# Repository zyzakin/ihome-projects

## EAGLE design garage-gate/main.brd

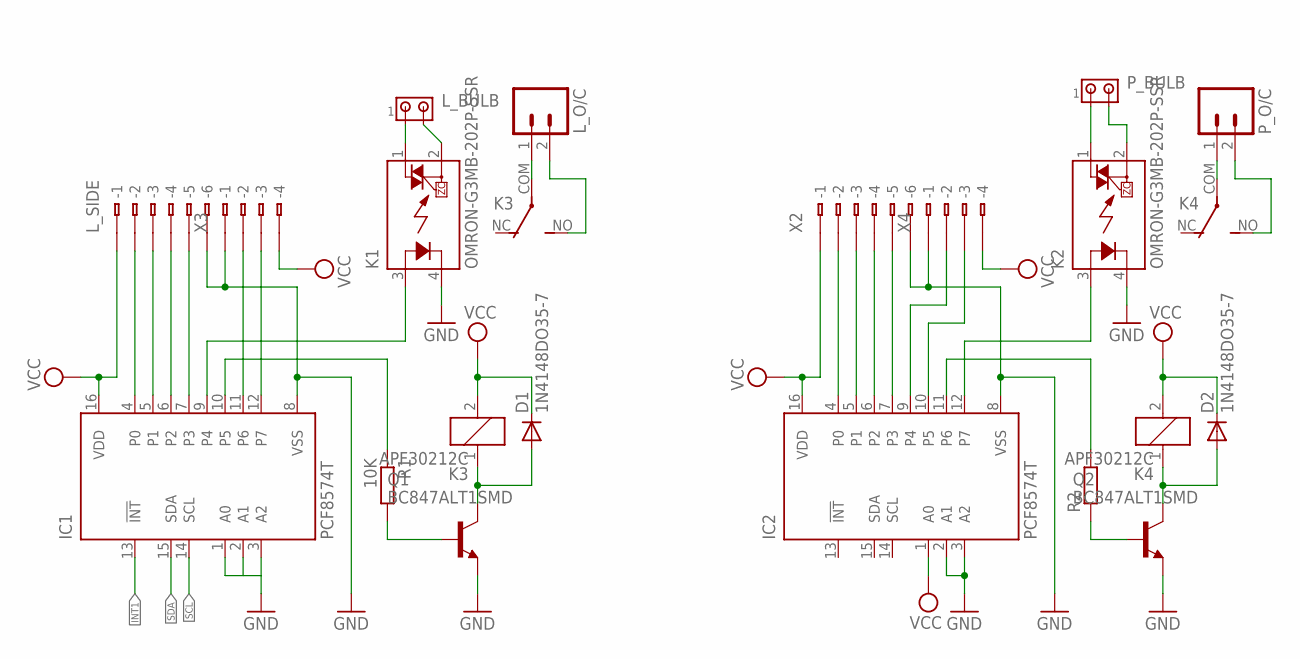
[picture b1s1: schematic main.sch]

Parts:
D1, D2: 1N4148DO35-7; DO35-7
IC1, IC2: PCF8574T; SO16W
K1, K2: OMRON-G3MB-202P-SSR
K3, K4: APF30212C
L_BULB: MTA02-156; 1X2MTA
L_O/C: M02; 02P
L_SIDE: 233-106
P_BULB: MTA02-156; 1X2MTA
P_O/C: M02; 02P
Q1, Q2: BC847ALT1SMD; SOT23
R1: 10K; R0805W
R2: R-EU_R0805W; R0805W
X2: 233-106
X3, X4: 233-104

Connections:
GND: IC1.1 (A0), IC1.2 (A1), IC1.3 (A2), IC1.8 (VSS), IC2.2 (A1), IC2.3 (A2), IC2.8 (VSS), K1.4 (K), K2.4 (K), L_SIDE.B6 (B-6), Q1.2 (E), Q2.2 (E), X2.B6 (B-6), X3.B1 (B-1), X4.B1 (B-1)
INT1: IC1.13 (!INT)
unnamed: IC1.4 (P0), L_SIDE.B2 (B-2)
unnamed: IC1.5 (P1), L_SIDE.B3 (B-3)
unnamed: IC1.6 (P2), L_SIDE.B4 (B-4)
unnamed: IC1.7 (P3), L_SIDE.B5 (B-5)
unnamed: IC1.12 (P7), X3.B3 (B-3)
unnamed: IC1.11 (P6), X3.B2 (B-2)
unnamed: IC1.9 (P4), K1.3 (A)
unnamed: K1.2 (DS2), L_BULB.2
unnamed: K1.1 (DS1), L_BULB.1
unnamed: K3.COM, L_O/C.1
unnamed: K3.NO (S), L_O/C.2
unnamed: IC1.10 (P5), R1.1
unnamed: Q1.1 (B), R1.2
unnamed: D1.A, K3.1, Q1.3 (C)
unnamed: IC2.7 (P3), X2.B5 (B-5)
unnamed: Q2.1 (B), R2.1
unnamed: K2.1 (DS1), P_BULB.1
unnamed: K4.COM, P_O/C.1
unnamed: D2.A, K4.1, Q2.3 (C)
unnamed: K4.NO (S), P_O/C.2
unnamed: IC2.12 (P7), K2.3 (A)
unnamed: IC2.11 (P6), R2.2
unnamed: IC2.10 (P5), X4.B3 (B-3)
unnamed: IC2.9 (P4), X4.B2 (B-2)
unnamed: IC2.6 (P2), X2.B4 (B-4)
unnamed: IC2.5 (P1), X2.B3 (B-3)
unnamed: IC2.4 (P0), X2.B2 (B-2)
unnamed: K2.2 (DS2), P_BULB.2
SCL: IC1.14 (SCL)
SDA: IC1.15 (SDA)
VCC: D1.C, D2.C, IC1.16 (VDD), IC2.1 (A0), IC2.16 (VDD), K3.2, K4.2, L_SIDE.B1 (B-1), X2.B1 (B-1), X3.B4 (B-4), X4.B4 (B-4)

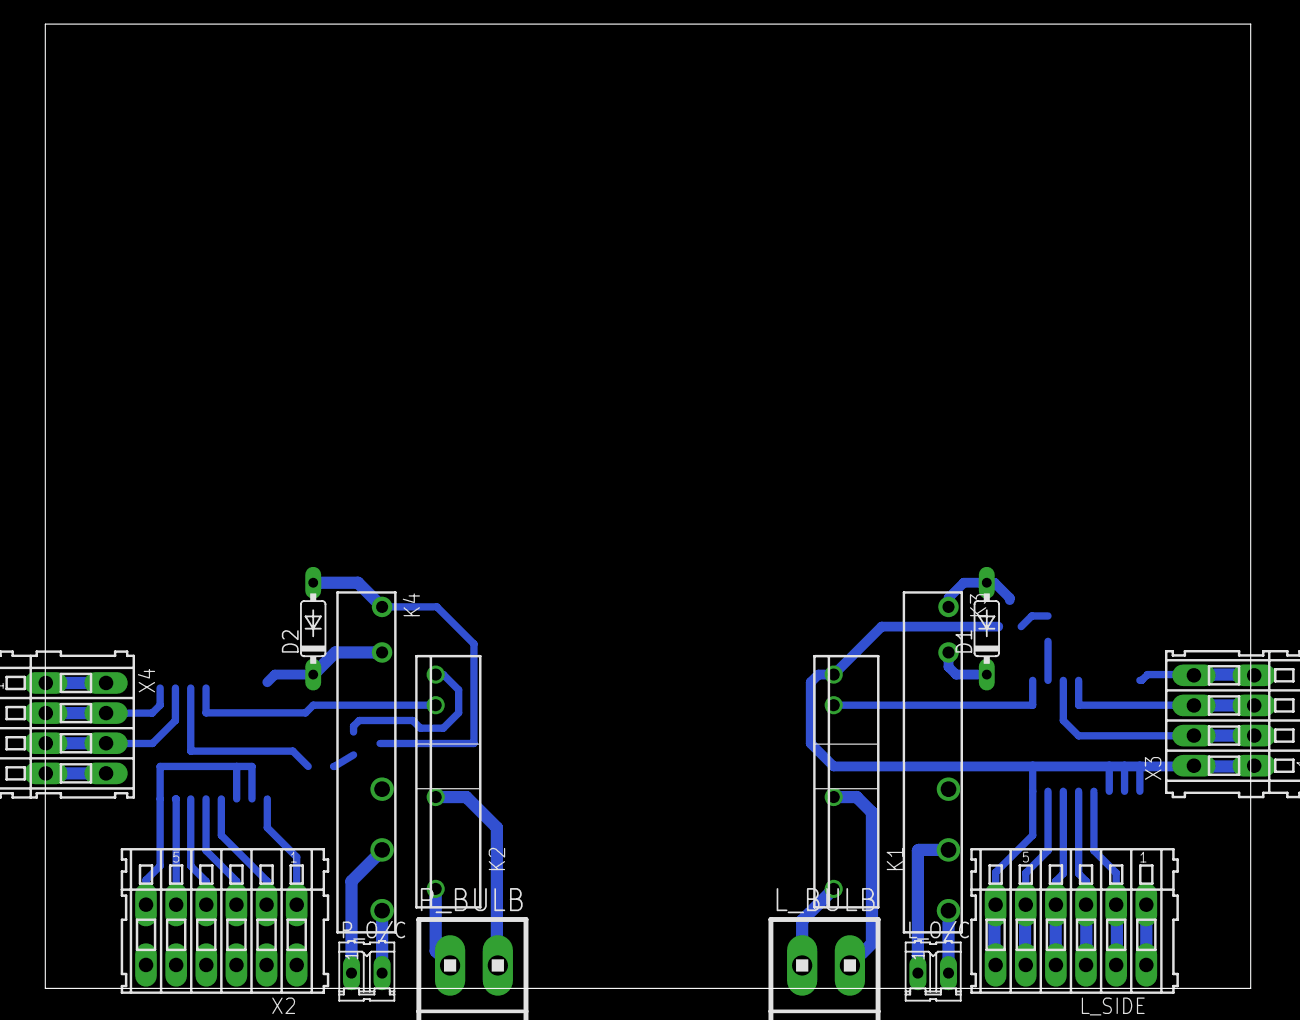
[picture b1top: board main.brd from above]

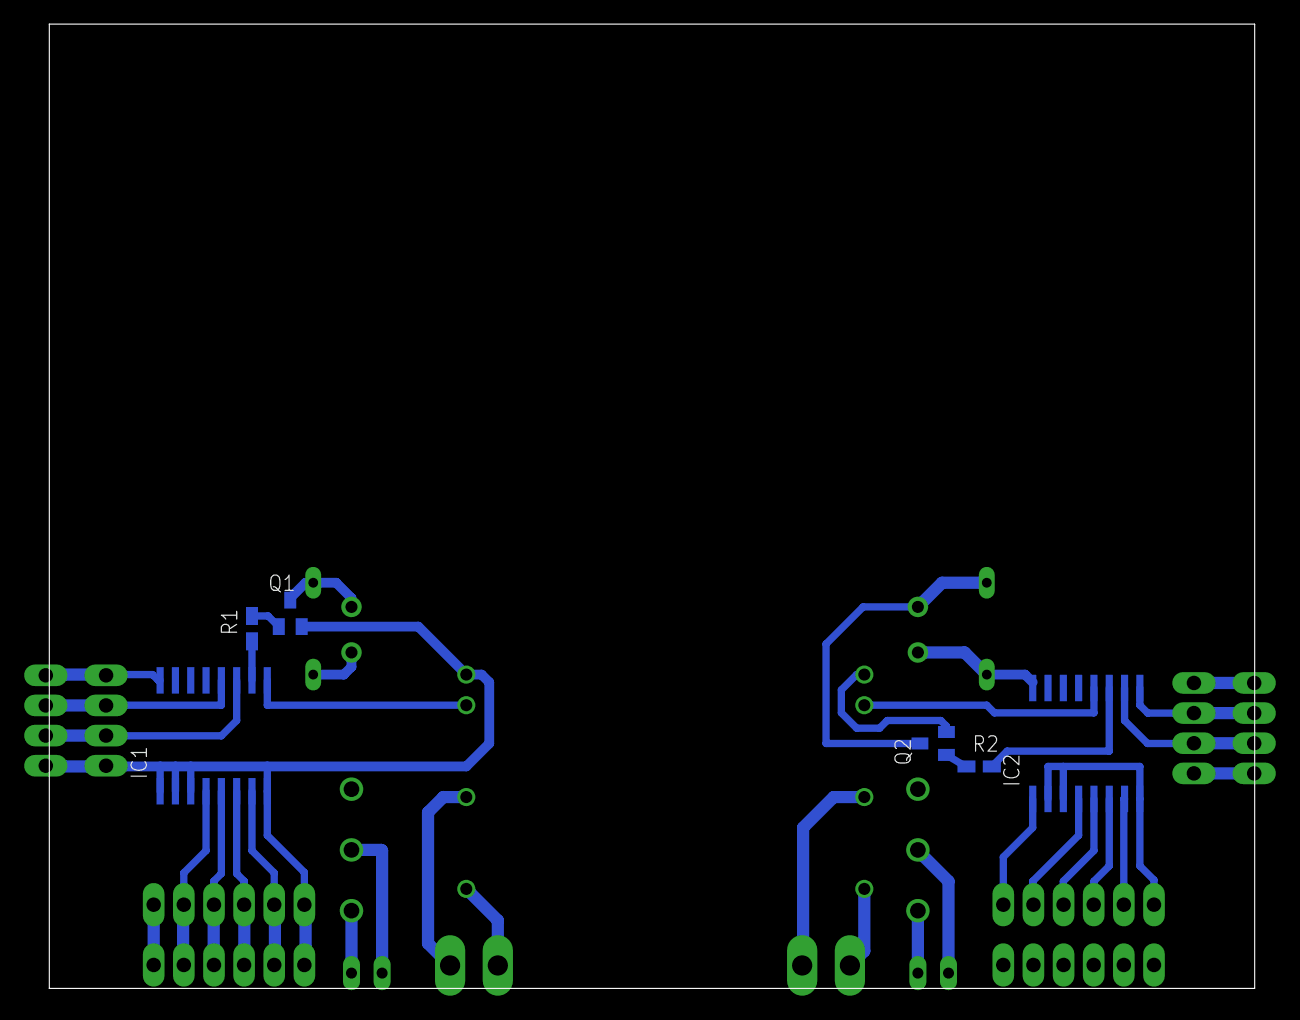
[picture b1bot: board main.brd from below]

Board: 2 copper layers, 100.0 x 80.0 mm, 20 parts (6 on the bottom side), 30 nets.

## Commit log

2017-11-02 init repo
2017-11-07 init

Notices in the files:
parts and their libraries:
SparkFun-Aesthetics: Licensing: Creative Commons ShareAlike 4.0 International - https://creativecommons.org/licenses/by-sa/4.0
